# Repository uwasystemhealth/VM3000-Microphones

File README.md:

# VM3000-Microphones

This project was completed by Ricky Leman under the supervision of Dr Ben Travaglione and Professor Melinda Hodkiewicz as part of the UWA Master of Professional Engineering research units GENG5511 & GENG5512.

This project involves the design, build and testing of a microphone array prototype which implements a pair of Vesper VM3000 MEMS microphones.

This repository and the time_domain_beamforming repository - https://github.com/uwasystemhealth/time_domain_beamforming contains all relevant files for the VM3000 PDM microphone array beamforming project.

All collected test data can be found in the time_domain_beamforming repository

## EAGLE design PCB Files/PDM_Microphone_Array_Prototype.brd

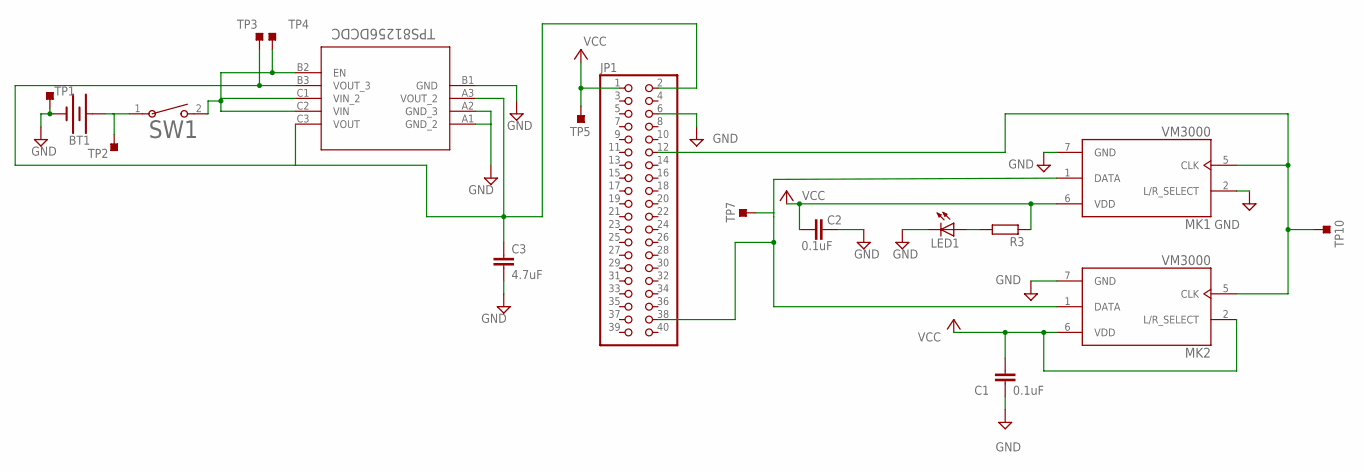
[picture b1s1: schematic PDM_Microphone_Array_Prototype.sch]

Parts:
BT1: BATTERY-18650; BATTERY_18650-HOLDER
C1, C2: 0.1uF; 0402
C3: 4.7uF; 1206
JP1: PINHD-2X20; 2X20
LED1: LEDCHIPLED_0805; CHIPLED_0805
MK1, MK2: VM3000; MIC_VM3000
R3: R-EU_R0805; R0805
SW1: GF-123-0054; SW2_GF-123-0054_CWI
TP1, TP2, TP3, TP4, TP5, TP7, TP10: TESTPOINT_TPS-PAD-036; TESTPOINT_PAD-036
TPS81256DCDC: TPS81256SIPRUSIP9_SIP_TEX-L; USIP9_SIP_TEX-L

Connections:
GND: BT1.GND@1 (-), C1.2, C2.1, C3.2, JP1.6, LED1.C, MK1.2 (L/R_SELECT), MK1.7 (GND), MK2.7 (GND), TP1.1, TPS81256DCDC.A1 (GND_2), TPS81256DCDC.A2 (GND_3), TPS81256DCDC.B1 (GND)
unnamed: JP1.38, MK1.1 (DATA), MK2.1 (DATA), TP7.1
unnamed: JP1.12, MK1.5 (CLK), MK2.5 (CLK), TP10.1
unnamed: LED1.A, R3.2
unnamed: SW1.2, TP4.1, TPS81256DCDC.B2 (EN), TPS81256DCDC.C1 (VIN_2), TPS81256DCDC.C2 (VIN)
unnamed: C3.1, JP1.2, TP3.1, TPS81256DCDC.A3 (VOUT_2), TPS81256DCDC.B3 (VOUT_3), TPS81256DCDC.C3 (VOUT)
unnamed: BT1.PWR@1 (+), SW1.1, TP2.1
VCC: C1.1, C2.2, JP1.1, MK1.6 (VDD), MK2.2 (L/R_SELECT), MK2.6 (VDD), R3.1, TP5.1

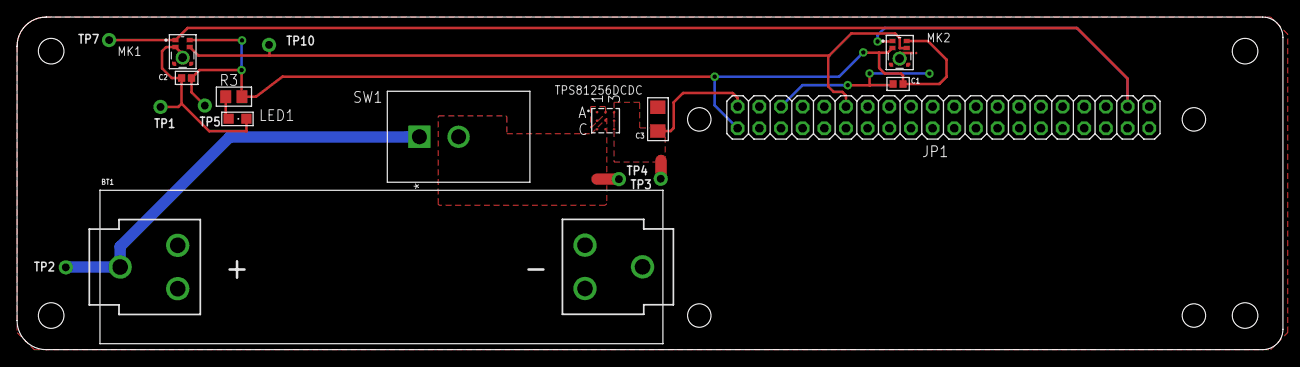
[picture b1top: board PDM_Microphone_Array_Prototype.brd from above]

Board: 2 copper layers, 148.4 x 39.0 mm, 18 parts (0 on the bottom side), 8 nets.

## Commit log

2020-07-29 Creating new file for Pi Zero W practice
2020-07-29 Rename untitled.txt to PiZeroWPractice.txt
2020-07-29 Test commit
2020-07-29 Updating Pi Zero W Practice file
2020-07-29 test
2020-07-29 Added note about inserting images
2020-07-30 Added Python script code and some images
2020-07-30 More updates
2020-07-30 Added next steps
2020-08-07 Adding TestFile
2020-08-07 Changed PiZeroW1 filename to ProgressTracking
2020-08-07 Minor update
2020-08-11 Minor updates
2020-08-14 Minor edits
2020-08-14 Added next step plans as of 14/08/2020
2020-08-26 Updated PDM section
2020-08-27 Progress update
2020-09-07 Latest updates
2020-09-11 Added notes on scp and audio
2020-09-11 Added info about extracting data from wav
2020-09-11 Added .gitignore
2020-09-15 added image test
2020-09-15 Added Images
2020-09-15 Replaced drag & drop images with HTML
2020-09-24 Added PDM setup section
2020-09-25 Updating PDM steps section
2020-09-29 Added prototype PCB design section
2020-09-29 Added PCB relevant images and files
2020-09-29 Minor typo fixes
2020-09-29 Added audio playground notebook
2020-10-02 Updated audio playground notebooks
2020-10-13 Added microphone array BOM
2020-10-16 Added new progress update section
2020-10-23 Added populated PCB prototype images
2020-10-23 Updated microphone array assembly section
2020-10-27 Updated microphone array functionality testing
2020-11-04 Added individual PDM mode setup instructions notebook
2020-11-04 Added individual PDM setup instruction notebook
2020-11-05 Improved PDM mode setup instructions
2020-11-13 Added tests for exploring microphone array characteristics
2020-11-13 Required equipment for testing updates
2021-02-26 Added code to conduct board frequency characterisation tests
2021-03-03 Signal Generation Testing
2021-03-10 Added progress update 7
2021-03-11 Written up more code
2021-03-12 Updated code
2021-03-12 More coding
2021-03-12 Added in plotting codes
2021-03-12 Added code
2021-05-16 Added notebook used for experimental data collection
    Used to control Keysight 33500B Waveform Generator, connect to RPi and collect test data.
    Used in UWA Anechoic Chamber and UWA SHL room.
2021-05-16 Added notebook used for initial signal generation and data collection prior to experimental trials.
2021-05-16 Cleaning folder
2021-05-16 Updated RPi PDM setup instructions
2021-05-16 Updated RPi PDM instructions
2021-05-16 Cleaning repo
2021-05-16 Adding relevant images
2021-05-16 Updated progress tracking
2021-05-16 Added experimenal setup images
2021-05-18 Replaced RaspberryPi_PDM_Instructions notebook with markdown file
2021-05-18 Remove ipynb_checkpoints files
2021-05-20 Deleted cached/three_sources_cache.h5

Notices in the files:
parts and their libraries:
SparkFun-Batteries: Licensing: Creative Commons ShareAlike 4.0 International - https://creativecommons.org/licenses/by-sa/4.0
COPYRIGHT: Copyright (C) 2018 Accelerated Designs. All rights reserved
